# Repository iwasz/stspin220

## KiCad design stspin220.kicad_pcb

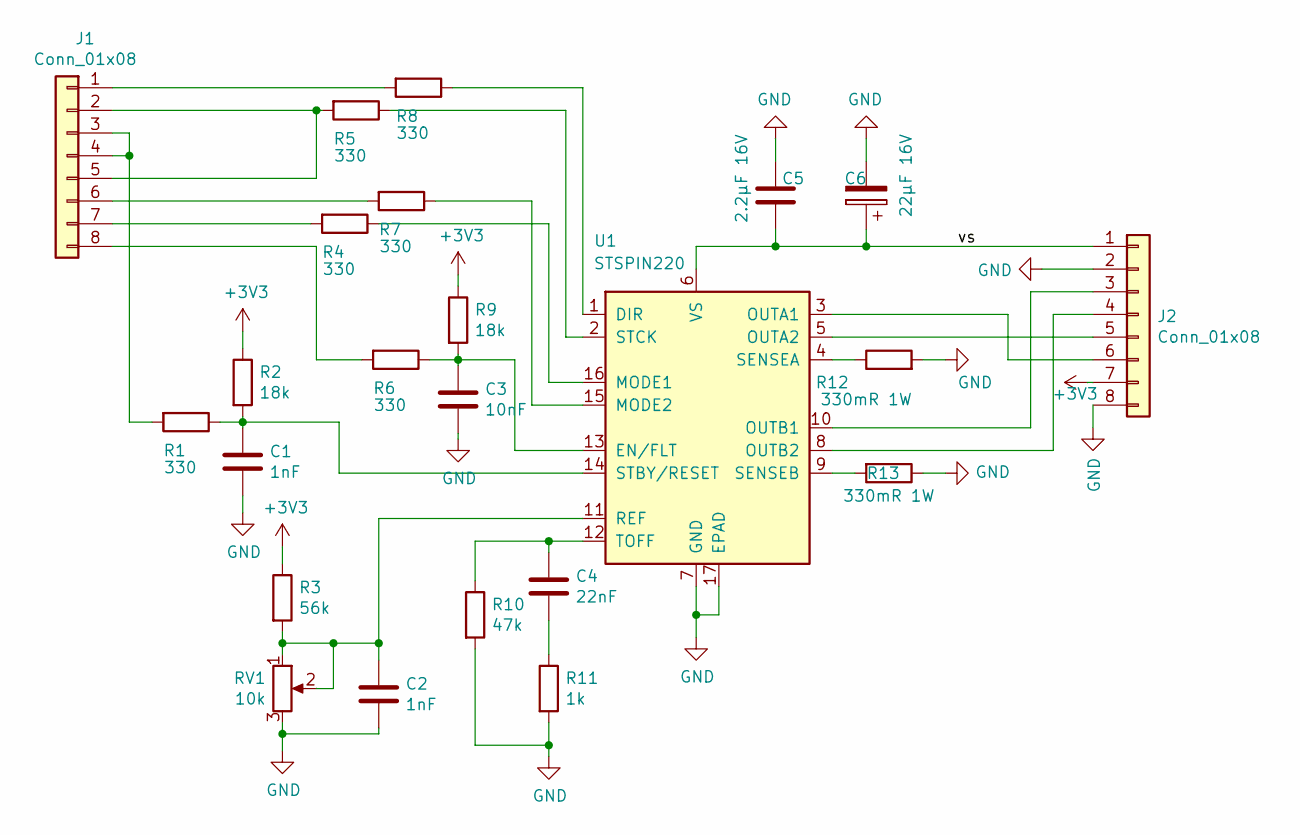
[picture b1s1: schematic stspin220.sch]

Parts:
C1, C2: 1nF; C_0402_1005Metric
C3: 10nF; C_0402_1005Metric
C4: 22nF; C_0402_1005Metric
C5: 2.2µF 16V; C_0603_1608Metric
C6: 22µF 16V; CP_EIA-3528-21_Kemet-B
J1, J2: Conn_01x08; PinHeader_1x08_P2.54mm_Vertical
R1, R4, R5, R6, R7, R8: 330; R_0402_1005Metric
R2, R9: 18k; R_0402_1005Metric
R3: 56k; R_0402_1005Metric
R10: 47k; R_0402_1005Metric
R11: 1k; R_0402_1005Metric
R12, R13: 330mR 1W; R_1206_3216Metric
RV1: 10k; Potentiometer_Bourns_3214W_Vertical
U1: STSPIN220; QFN-16-1EP_3x3mm_P0.5mm_EP1.8x1.8mm

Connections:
+3V3: J2.7, R2.1, R3.1, R9.1
/vs: C5.2, C6.1, J2.1, U1.6 (VS)
GND: C1.2, C2.2, C3.2, C5.1, C6.2, J2.2, J2.8, R10.2, R11.2, R12.2, R13.1, RV1.3, U1.7 (GND), U1.17 (EPAD)
unnamed: C1.1, R1.1, R2.2, U1.14 (STBY/RESET)
unnamed: C2.1, R3.2, RV1.1, RV1.2, U1.11 (REF)
unnamed: C3.1, R6.1, R9.2, U1.13 (EN/FLT)
unnamed: C4.1, R10.1, U1.12 (TOFF)
unnamed: C4.2, R11.1
unnamed: J1.1, R8.2
unnamed: J1.2, J1.5, R5.2
unnamed: J1.3, J1.4, R1.2
unnamed: J1.6, R7.2
unnamed: J1.7, R4.2
unnamed: J1.8, R6.2
unnamed: J2.3, U1.10 (OUTB1)
unnamed: J2.4, U1.8 (OUTB2)
unnamed: J2.5, U1.5 (OUTA2)
unnamed: J2.6, U1.3 (OUTA1)
unnamed: R4.1, U1.16 (MODE1)
unnamed: R5.1, U1.2 (STCK)
unnamed: R7.1, U1.15 (MODE2)
unnamed: R8.1, U1.1 (DIR)
unnamed: R12.1, U1.4 (SENSEA)
unnamed: R13.2, U1.9 (SENSEB)

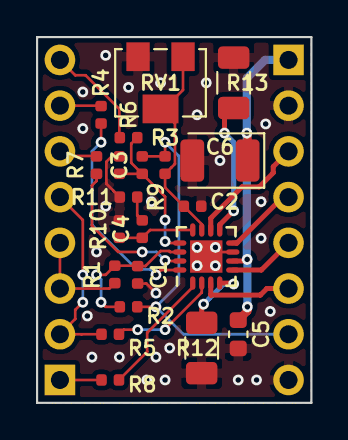
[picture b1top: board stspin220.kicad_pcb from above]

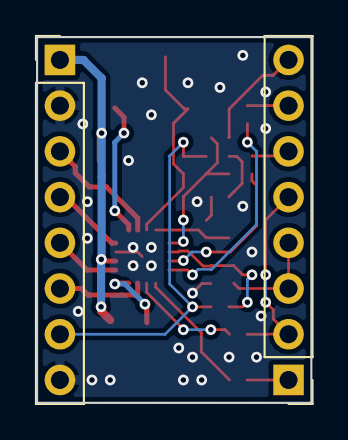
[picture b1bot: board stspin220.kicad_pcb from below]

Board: 2 copper layers, 15.2 x 20.3 mm, 23 parts (2 on the bottom side), 24 nets.

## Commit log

2018-10-10 First commit.
